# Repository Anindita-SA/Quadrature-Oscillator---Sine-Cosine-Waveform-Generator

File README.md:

# Quadrature Oscillator - Sine/Cosine Waveform Generator

⚠️ **WORK IN PROGRESS** - Hardware optimization ongoing

## Overview

1kHz quadrature oscillator generating simultaneous sine and cosine waveforms with 90° phase relationship using op-amp integrators.

**Key Specs:**
- Frequency: 1 kHz
- Phase Difference: 90° (quadrature)
- Output: ~2.4V peak
- Supply: ±15V
- IC: LM358 dual op-amp

## Circuit Design

### Topology

State-variable quadrature oscillator implementing:

```
d(sine)/dt = ω × cosine
d(cosine)/dt = -ω × sine
```

### Schematic

[Final PCB for 1khz Sine wave generator 2.pdf](https://github.com/user-attachments/files/23353181/Final.PCB.for.1khz.Sine.wave.generator.2.pdf)

### Components

| Component | Value | Function |
|-----------|-------|----------|
| R1, R2, R3, R4 | 1.6kΩ | Frequency setting |
| C1, C2, C3 | 100nF | Integrator capacitors |
| R5, R7 | 1kΩ | Bias network |
| R6, R10 | 8kΩ | Voltage divider |
| D1, D2 | 1N4148 | Amplitude limiting |
| U1, U2 | LM358 | Op-amps (2 ICs) |

## Calculations

**Frequency:**
```
f = 1/(2πRC) = 1/(2π × 1.6kΩ × 100nF) ≈ 995 Hz
Measured: 1.01 kHz (±1%)
```

**Output Amplitude:**
```
V_bias = 15V × 1kΩ/9kΩ = 1.67V
V_peak = V_bias + V_diode = 1.67V + 0.7V = 2.37V
Measured: ~2.4V ✓
```

**Phase:**
```
Target: 90°
Measured: 83-85° (within tolerance)
```

## Performance

| Parameter | Target | Simulation | Hardware |
|-----------|--------|------------|----------|
| Frequency | 1000 Hz | 1009 Hz | 1030 Hz |
| Phase | 90° | 91.7° | 83-85° |
| Amplitude | ~5V pp | 4.68V pp | ~2.4V |

## Design Evolution

1. **Wien Bridge** → Abandoned (complex amplitude control)
2. **All-Pass Filter** → Abandoned (wrong phase shift)
3. **Quadrature Oscillator** → Current (functional, optimizing)

## Known Issues

- **Hardware distortion** - LM358 slew rate limiting + breadboard parasitics
- **Phase accuracy** - Component tolerances cause 5-7° deviation
- **Amplitude variation** - Working on stabilization

## To-Do

- [ ] PCB implementation
- [ ] Add frequency adjustment potentiometer

## Files

- [[schematic.png](https://github.com/Anindita-SA/Quadrature-Oscillator-Sine-Cosine-Waveform-Generator/blob/61d378de57019a960dd601e74cefbcc4ff721f99/Final%20PCB%20for%201khz%20Sine%20wave%20generator%202.pdf)] - Circuit diagram
- [[simulation.asc](https://github.com/Anindita-SA/Quadrature-Oscillator-Sine-Cosine-Waveform-Generator/tree/61d378de57019a960dd601e74cefbcc4ff721f99/LTSpice%20simulation%20for%201kHz%20SineCosine%20Generator)] - LTspice file
- `calculations.md` - Design math
- `troubleshooting.md` - Issues log

## Build Notes

**Critical:**
- Use **film capacitors** for C1, C2, C3 (not ceramic)
- Verify component markings ("103" = 10nF, "104" = 100nF)
- Add 0.1µF decoupling caps close to IC pins
- Keep wires short on breadboard

## References

- Horowitz & Hill, "Art of Electronics" (3rd Ed., §5.17)
- [YouTube reference video](https://www.youtube.com/watch?v=ud4fuO_mj5U&t=720s&pp=ygU1cXVhZHJhdHVyZSBvc2NpbGxhdG9yIHVzaW5nIG9wIGFtcCBsdHNwaWNlIHNpbXVsYXRpb24%3D)

## License

Educational/open source - standard quadrature oscillator topology

## Contact

[[Github](https://github.com/Anindita-SA)]

**Status:** Active development - contributions welcome

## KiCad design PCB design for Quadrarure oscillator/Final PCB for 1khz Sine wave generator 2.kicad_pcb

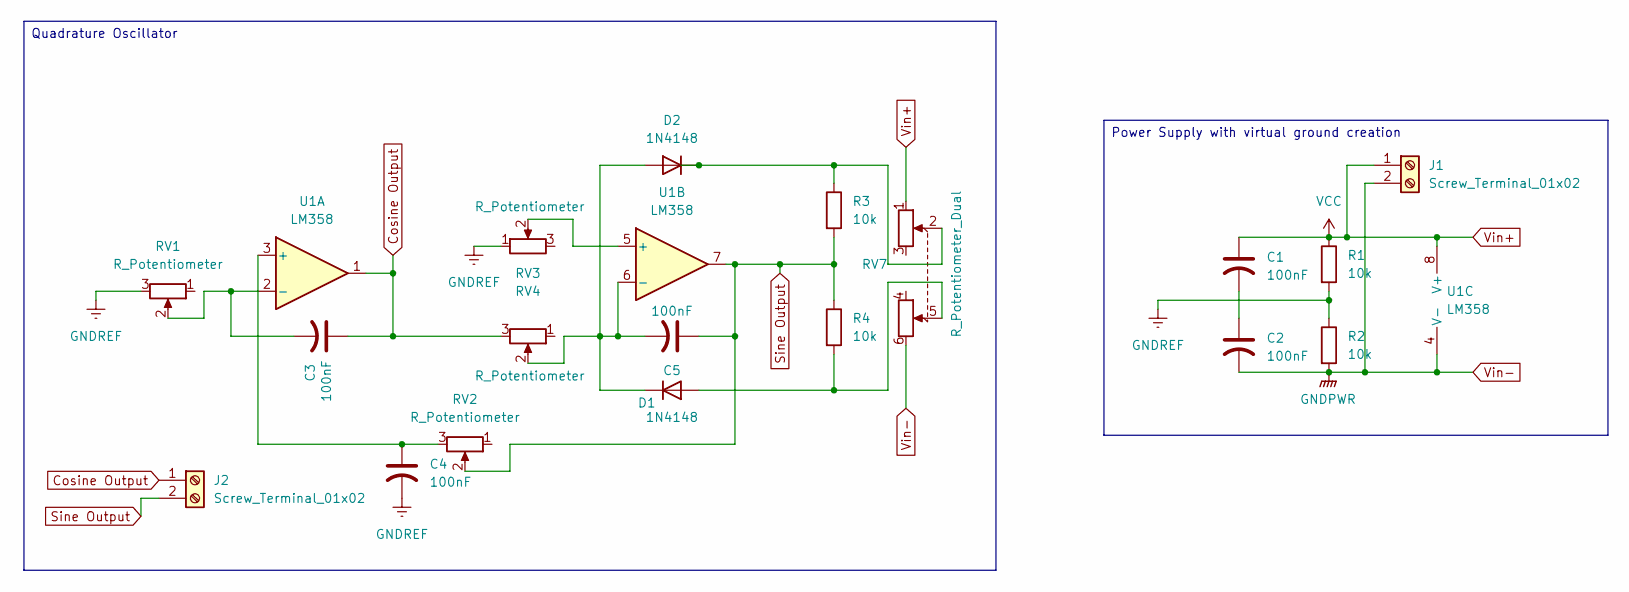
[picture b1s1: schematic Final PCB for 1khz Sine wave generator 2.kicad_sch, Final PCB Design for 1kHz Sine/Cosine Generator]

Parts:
C1, C2, C3, C4, C5: 100nF; C_Disc_D3.8mm_W2.6mm_P2.50mm
D1, D2: 1N4148; D_DO-35_SOD27_P7.62mm_Horizontal
J1, J2: Screw_Terminal_01x02; TerminalBlock_Phoenix_MKDS-1,5-2-5.08_1x02_P5.08mm_Horizont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
R1, R2, R3, R4: 10k; R_Axial_DIN0204_L3.6mm_D1.6mm_P5.08mm_Horizontal
RV1, RV2, RV3, RV4: R_Potentiometer; Potentiometer_Bourns_3266Y_Vertical
RV7: R_Potentiometer_Dual; Potentiometer_Alps_RK163_Dual_Horizontal
U1: LM358; DIP-8_W7.62mm_Socket_LongPads

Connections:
Cosine Output: C3.1, J2.1, RV4.3, U1.1
GNDREF: C4.2, R1.2, R2.1, RV1.3, RV3.1
unnamed: C1.2, C2.1
unnamed: D1.2 (A), R4.2, RV7.5
unnamed: C5.2, D1.1 (K), D2.2 (A), RV4.2, U1.6 (-)
unnamed: D2.1 (K), R3.1, RV7.2
unnamed: C4.1, RV2.3, U1.3 (+)
unnamed: C3.2, RV1.2, U1.2 (-)
unnamed: RV3.2, U1.5 (+)
Sine Output: C5.1, J2.2, R3.2, R4.1, RV2.2, U1.7
Vin+: C1.1, J1.1, R1.1, RV7.1, U1.8 (V+)
Vin-: C2.2, J1.2, R2.2, RV7.6, U1.4 (V-)

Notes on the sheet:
Power Supply with virtual ground creation
Quadrature Oscillator

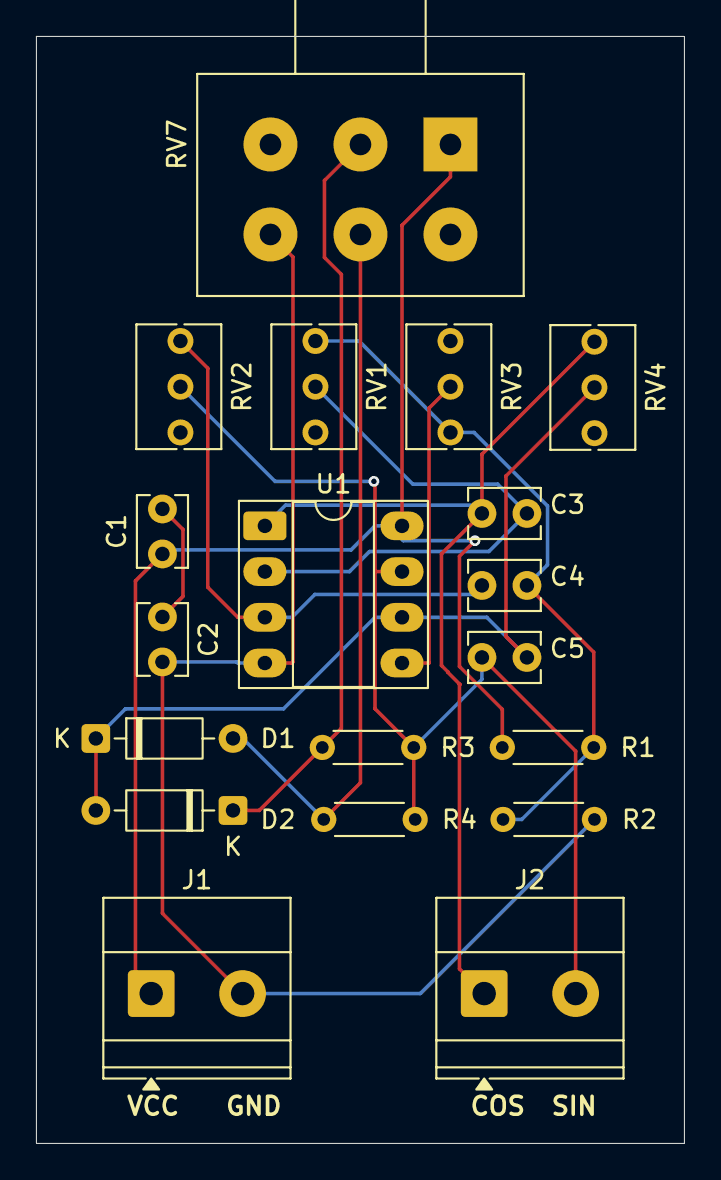
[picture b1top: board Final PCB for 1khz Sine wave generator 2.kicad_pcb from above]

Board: 2 copper layers, 36.0 x 61.5 mm, 19 parts (0 on the bottom side), 12 nets.

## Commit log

2025-11-05 Fix formatting of file links in README
